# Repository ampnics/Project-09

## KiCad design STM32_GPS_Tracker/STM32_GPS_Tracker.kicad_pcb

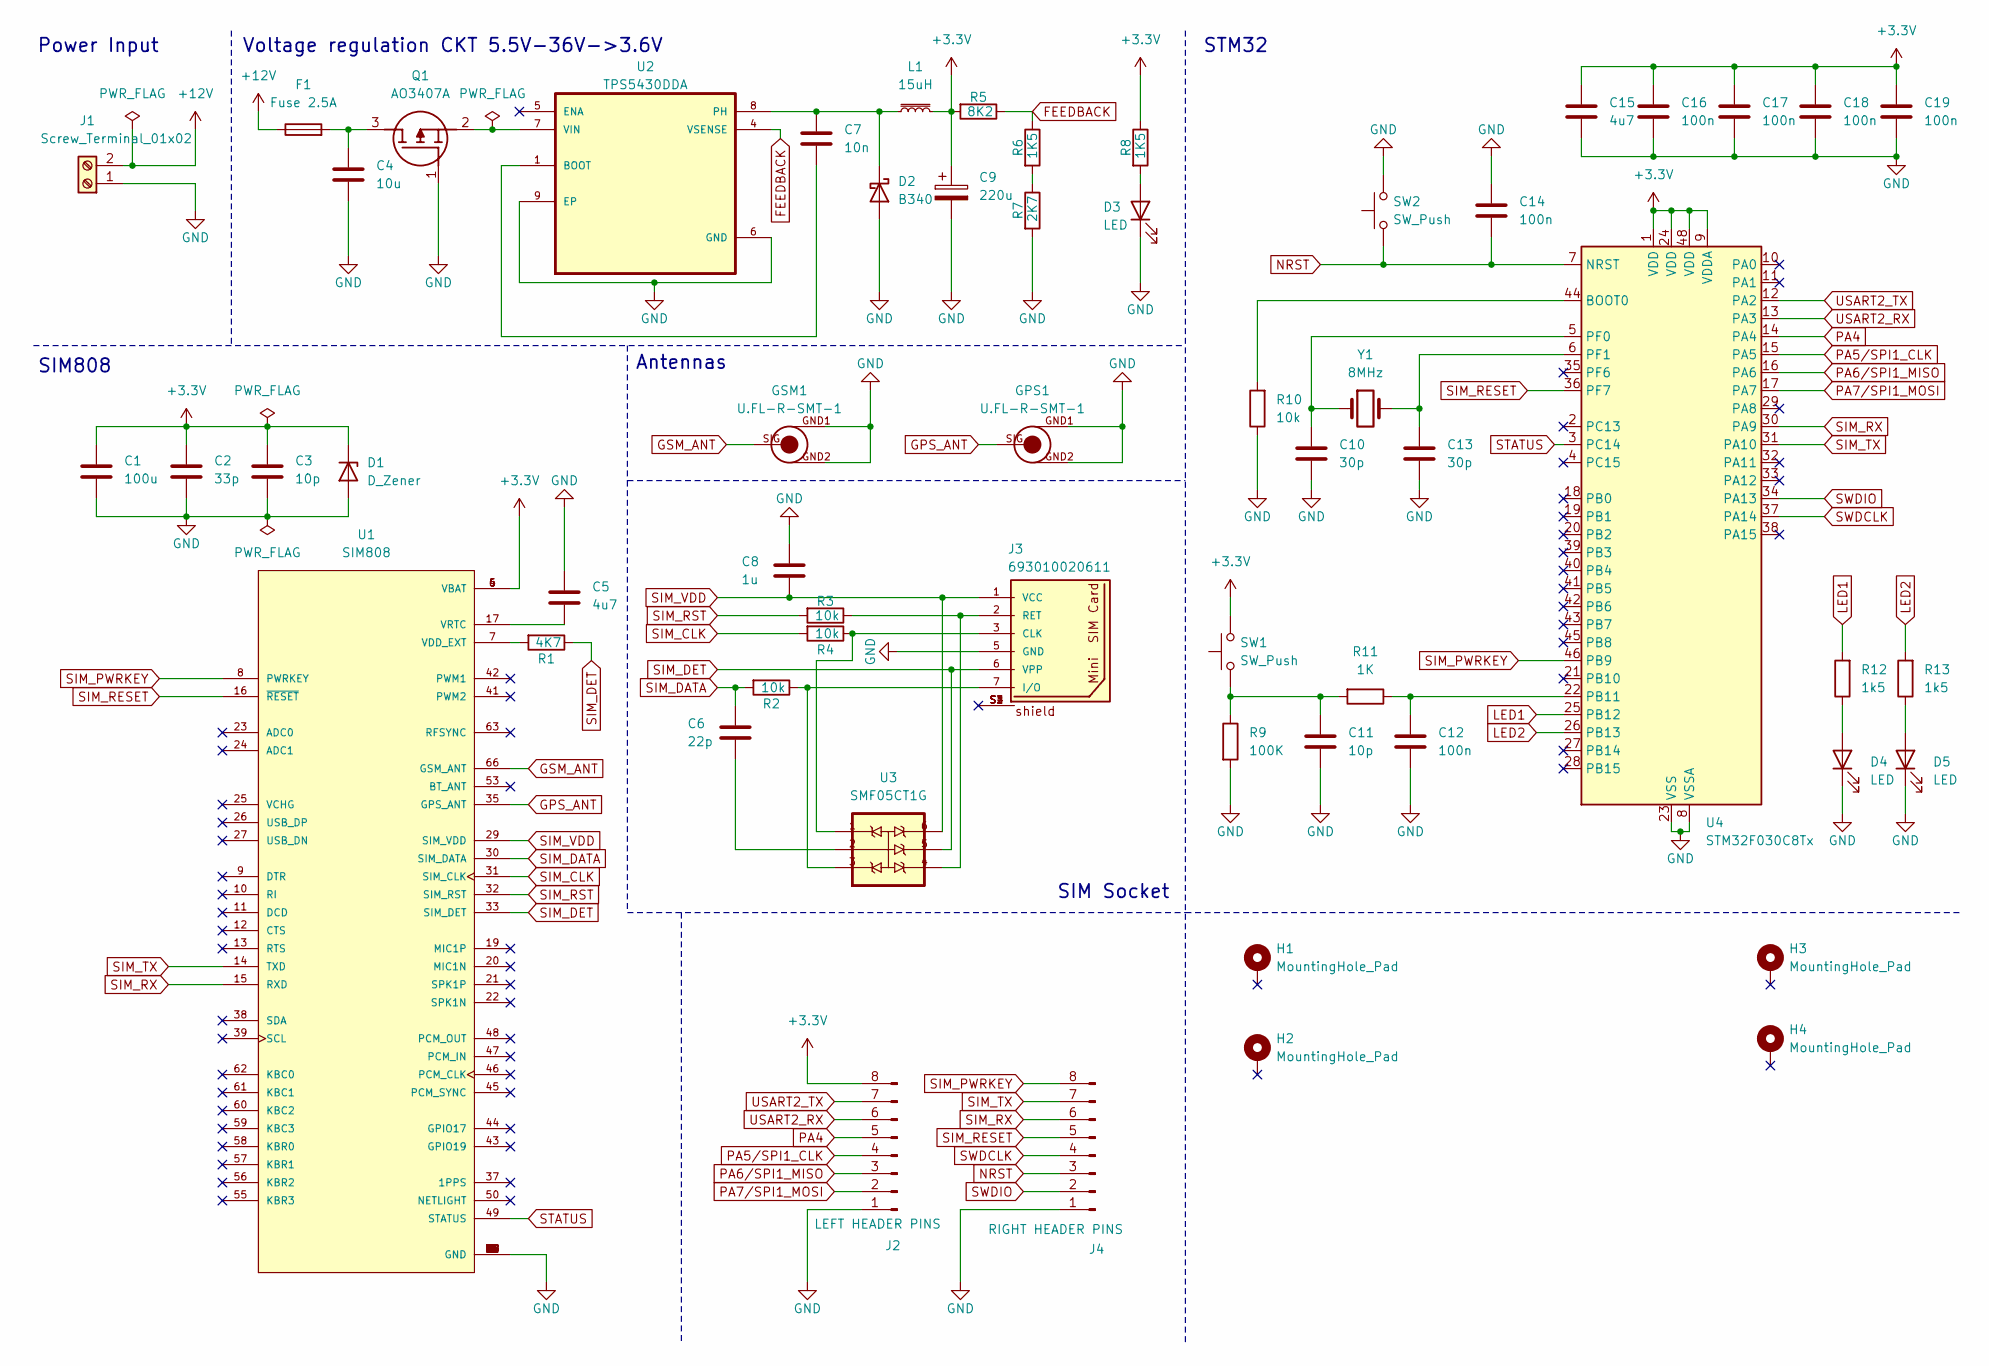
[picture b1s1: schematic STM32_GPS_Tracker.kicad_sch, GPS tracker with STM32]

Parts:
C1: 100u; C_1206_3216Metric
C2: 33p; C_0402_1005Metric
C3, C11: 10p; C_0402_1005Metric
C4: 10u; C_0805_2012Metric
C5, C15: 4u7; C_0201_0603Metric
C6: 22p; C_0402_1005Metric
C7: 10n; C_0201_0603Metric
C8: 1u; C_0402_1005Metric
C9: 220u; CP_EIA-7343-15_Kemet-W
C10, C13: 30p; C_0402_1005Metric
C12, C14, C16, C17, C18, C19: 100n; C_0402_1005Metric
D1: D_Zener; D_0805_2012Metric
D2: B340; D_SMC
D3, D4, D5: LED; LED_0603_1608Metric
F1: Fuse 2.5A; Fuse_0402_1005Metric
GPS1: U.FL-R-SMT-1
GSM1: U.FL-R-SMT-1
H1, H2, H3, H4: MountingHole_Pad; MountingHole_2.2mm_M2_Pad_Via
J1: Screw_Terminal_01x02; TerminalBlock_bornier-2_P5.08mm
J2: LEFT HEADER PINS; PinHeader_1x08_P2.54mm_Vertical
J3: 693010020611; PART-NUMBER 693010020611
J4: RIGHT HEADER PINS; PinHeader_1x08_P2.54mm_Vertical
L1: 15uH; L_10.4x10.4_H4.8
Q1: AO3407A; SOT95P280X125-3N; Manufacturer_Part_Number AO3407A
R1: 4K7; R_0402_1005Metric
R2, R3, R4, R10: 10k; R_0402_1005Metric
R5: 8K2; R_0805_2012Metric
R6, R8: 1K5; R_0805_2012Metric
R7: 2K7; R_0805_2012Metric
R9: 100K; R_0201_0603Metric
R11: 1K; R_0603_1608Metric
R12, R13: 1k5; R_0805_2012Metric
SW1, SW2: SW_Push; SW_Push_1P1T_NO_CK_KSC6xxJ
U1: SIM808; XCVR_SIM808; PARTREV 1.03
U2: TPS5430DDA; VREG_LM5017MR_NOPB
U3: SMF05CT1G; SOT65P210X110-6N
U4: STM32F030C8Tx; LQFP-48_7x7mm_P0.5mm
Y1: 8MHz; Crystal_SMD_5032-2Pin_5.0x3.2mm

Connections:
+3.3V: C1.1, C2.1, C3.1, C9.1, C15.1, C16.1, C17.1, C18.1, C19.1, D1.1 (K), J2.8, L1.2, R5.2, R8.1, SW1.2, U1.4 (VBAT), U1.5 (VBAT), U1.6 (VBAT), U4.1 (VDD), U4.9 (VDDA), U4.24 (VDD), U4.48 (VDD); also elsewhere on the board
+12V: F1.1, J1.2
FEEDBACK: R5.1, R6.1, U2.4 (VSENSE)
GND: C1.2, C2.2, C3.2, C4.2, C5.1, C8.1, C9.2, C10.2, C11.2, C12.2, C13.2, C14.1, C15.2, C16.2, C17.2, C18.2, C19.2, D1.2 (A), D2.2 (A), D3.1 (K), D4.1 (K), D5.1 (K), GPS1.GND1, GPS1.GND2, GSM1.GND1, GSM1.GND2, J1.1, J2.1, J3.5 (GND), J4.1, Q1.1 (G), R7.2, R9.2, R10.1, SW2.2, U1.1 (GND), U1.2 (GND), U1.3 (GND), U1.18 (GND), U1.28 (GND), U1.34 (GND), U1.36 (GND), U1.40 (GND), U1.51 (GND), U1.52 (GND), U1.54 (GND), U1.64 (GND), U1.65 (GND), U1.67 (GND), U1.68 (GND), U2.6 (GND), U2.9 (EP), U4.8 (VSSA), U4.23 (VSS), U4.47 (VSS); also elsewhere on the board
GPS_ANT: GPS1.SIG, U1.35 (GPS_ANT)
GSM_ANT: GSM1.SIG, U1.66 (GSM_ANT)
LED1: R12.2, U4.25 (PB12)
LED2: R13.2, U4.26 (PB13)
NRST: C14.2, J4.3, SW2.1, U4.7 (NRST); also elsewhere on the board
unnamed: C6.2, U3.2
unnamed 10: C11.1, R9.1, R11.2, SW1.1; also elsewhere on the board
unnamed: C7.2, D2.1 (K), L1.1, U2.8 (PH)
unnamed: D3.2 (A), R8.2
unnamed: D4.2 (A), R12.1
unnamed: D5.2 (A), R13.1
unnamed: J3.3 (CLK), R4.1, U3.1
unnamed: J3.7 (I/O), R2.1, U3.3
unnamed: J3.2 (RET), R3.1, U3.4
unnamed: C4.1, F1.2, Q1.3 (D)
unnamed: Q1.2 (S), U2.7 (VIN)
unnamed: R6.2, R7.1
unnamed: R1.2, U1.7 (VDD_EXT)
unnamed: C5.2, U1.17 (VRTC)
unnamed: C7.1, U2.1 (BOOT)
unnamed: R10.2, U4.44 (BOOT0)
unnamed: C12.1, R11.1, U4.22 (PB11)
unnamed: C10.1, U4.5 (PF0), Y1.1
unnamed: C13.1, U4.6 (PF1), Y1.2
PA4: J2.5, U4.14 (PA4)
PA5/SPI1_CLK: J2.4, U4.15 (PA5)
PA6/SPI1_MISO: J2.3, U4.16 (PA6)
PA7/SPI1_MOSI: J2.2, U4.17 (PA7)
SIM_CLK: R4.2, U1.31 (SIM_CLK)
SIM_DATA: C6.1, R2.2, U1.30 (SIM_DATA)
SIM_DET: J3.6 (VPP), R1.1, U1.33 (SIM_DET), U3.5
SIM_PWRKEY: J4.8, U1.8 (PWRKEY), U4.46 (PB9)
SIM_RESET: J4.5, U1.16 (~RESET), U4.36 (PF7)
SIM_RST: R3.2, U1.32 (SIM_RST)
SIM_RX: J4.6, U1.15 (RXD), U4.30 (PA9)
SIM_TX: J4.7, U1.14 (TXD), U4.31 (PA10)
SIM_VDD: C8.2, J3.1 (VCC), U1.29 (SIM_VDD), U3.6
STATUS: U1.49 (STATUS), U4.3 (PC14)
SWDCLK: J4.4, U4.37 (PA14)
SWDIO: J4.2, U4.34 (PA13)
USART2_RX: J2.6, U4.13 (PA3)
USART2_TX: J2.7, U4.12 (PA2)

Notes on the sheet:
SIM Socket
Power Input
Voltage regulation CKT 5.5V-36V->3.6V
STM32
Antennas
SIM808

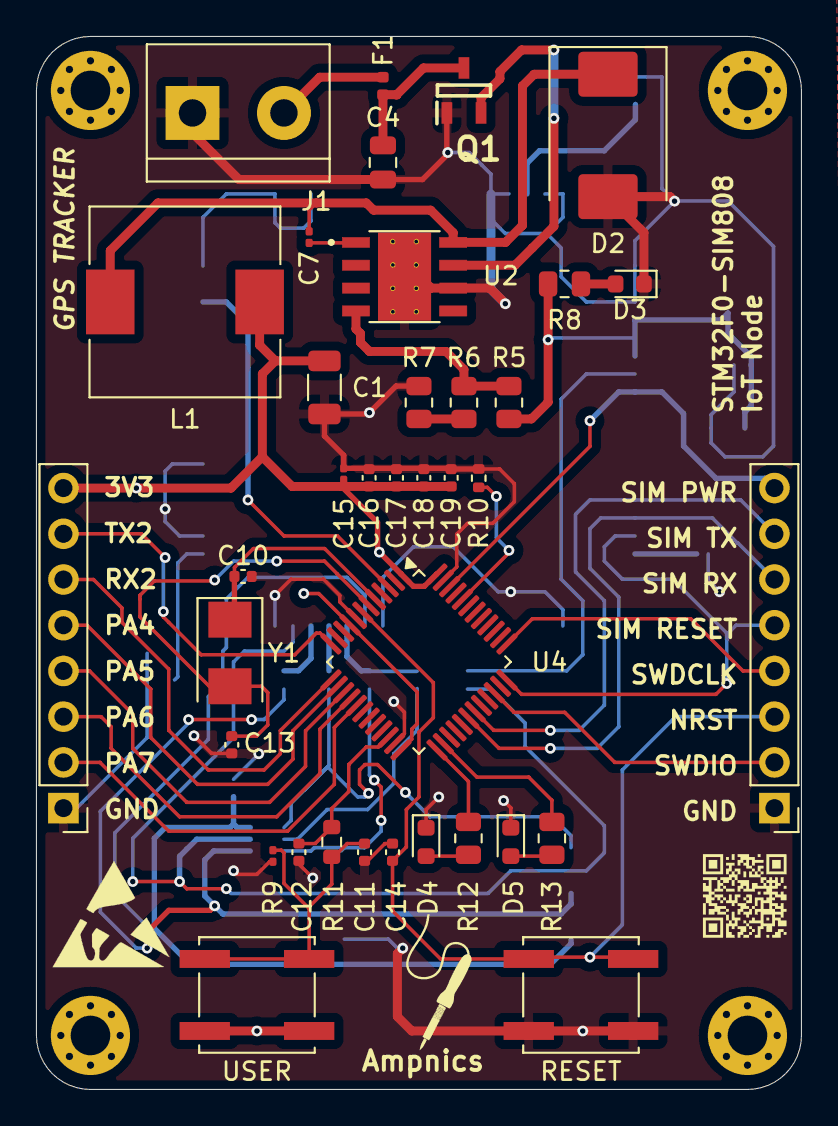
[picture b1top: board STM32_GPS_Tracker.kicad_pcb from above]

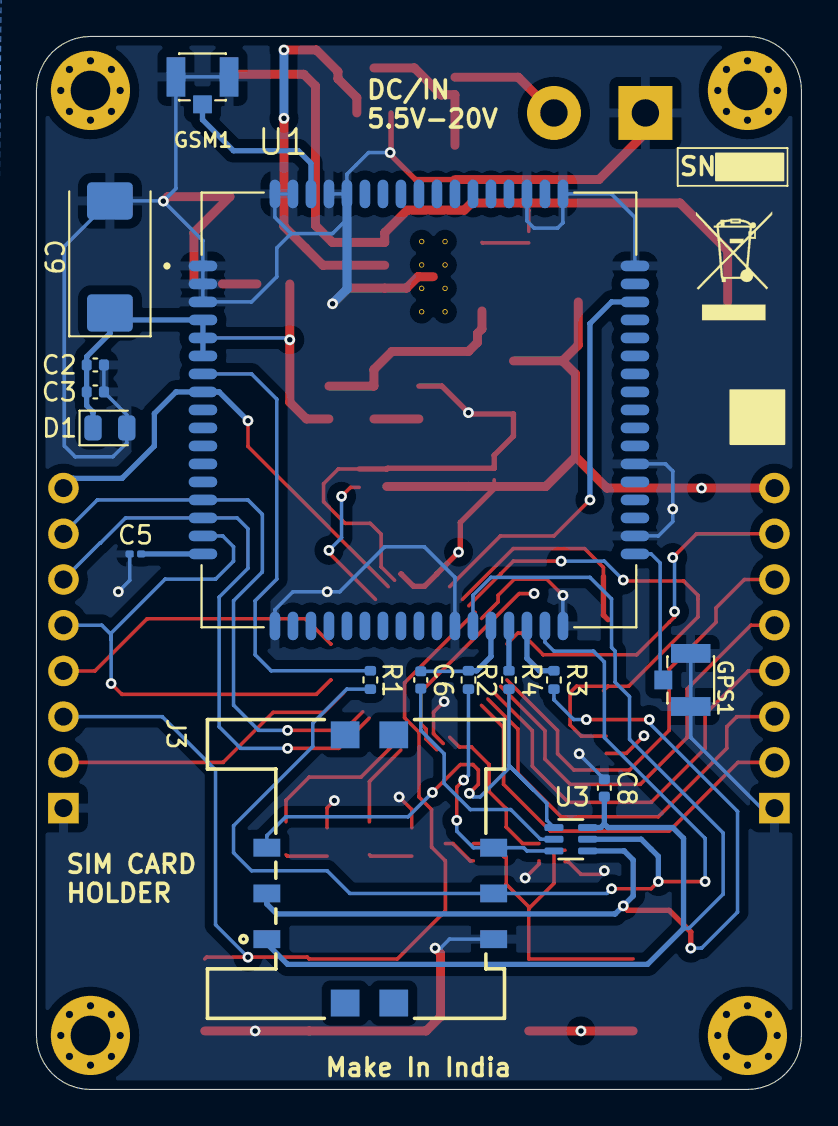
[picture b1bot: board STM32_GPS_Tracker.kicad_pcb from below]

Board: 4 copper layers, 42.5 x 58.5 mm, 57 parts (16 on the bottom side), 46 nets.

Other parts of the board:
RESET: SW_Push; SW_Push_1P1T_NO_CK_KSC6xxJ
USER: SW_Push; SW_Push_1P1T_NO_CK_KSC6xxJ

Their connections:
+3.3V: USER.2; also elsewhere on the board
GND: RESET.2; also elsewhere on the board
NRST: RESET.1; also elsewhere on the board
unnamed 10: USER.1; also elsewhere on the board

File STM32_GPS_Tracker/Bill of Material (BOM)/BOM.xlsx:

Reference | Value | Footprint | Qty
C1 | 100u | Capacitor_SMD:C_1206_3216Metric | 1
C2 | 33p | Capacitor_SMD:C_0402_1005Metric | 1
C3,C11 | 10p | Capacitor_SMD:C_0402_1005Metric | 2
C4 | 10u | Capacitor_SMD:C_0805_2012Metric | 1
C5,C15 | 4u7 | Capacitor_SMD:C_0201_0603Metric | 2
C6 | 22p | Capacitor_SMD:C_0402_1005Metric | 1
C7 | 10n | Capacitor_SMD:C_0201_0603Metric | 1
C8 | 1u | Capacitor_SMD:C_0402_1005Metric | 1
C9 | 220u | Capacitor_Tantalum_SMD:CP_EIA-7343-15_Kemet-W | 1
C10,C13 | 30p | Capacitor_SMD:C_0402_1005Metric | 2
C12,C14,C16,C17,C18,C19 | 100n | Capacitor_SMD:C_0402_1005Metric | 6
D1 | D_Zener | Diode_SMD:D_0805_2012Metric | 1
D2 | B340 | Diode_SMD:D_SMC | 1
D3,D4,D5 | LED | LED_SMD:LED_0603_1608Metric | 3
F1 | Fuse 2.5A | Fuse:Fuse_0402_1005Metric | 1
GPS1,GSM1 | U.FL-R-SMT-1 | U.FL-R-SMT-1:U.FL-R-SMT-1 | 2
J1 | Screw_Terminal_01x02 | TerminalBlock:TerminalBlock_bornier-2_P5.08mm | 1
J2 | LEFT HEADER PINS | Connector_PinHeader_2.54mm:PinHeader_1x08_P2.54mm_Vertical | 1
J3 | 693000000000 | 693010020611:693010020611 | 1
J4 | RIGHT HEADER PINS | Connector_PinHeader_2.54mm:PinHeader_1x08_P2.54mm_Vertical | 1
L1 | 15uH | Inductor_SMD:L_10.4x10.4_H4.8 | 1
Q1 | AO3407A | LIB_AO3407A:SOT95P280X125-3N | 1
R1 | 4K7 | Resistor_SMD:R_0402_1005Metric | 1
R2,R3,R4,R10 | 10k | Resistor_SMD:R_0402_1005Metric | 4
R5 | 8K2 | Resistor_SMD:R_0805_2012Metric | 1
R6,R8 | 1K5 | Resistor_SMD:R_0805_2012Metric | 2
R7 | 2K7 | Resistor_SMD:R_0805_2012Metric | 1
R9 | 100K | Resistor_SMD:R_0201_0603Metric | 1
R11 | 1K | Resistor_SMD:R_0603_1608Metric | 1
R12,R13 | 1k5 | Resistor_SMD:R_0805_2012Metric | 2
SW1,SW2 | SW_Push | Button_Switch_SMD:SW_Push_1P1T_NO_CK_KSC6xxJ | 2
U1 | SIM808 | SIM808:XCVR_SIM808 | 1
U2 | TPS5430DDA | TPS5430DDA:VREG_LM5017MR_NOPB | 1
U3 | SMF05CT1G | SMF05CT1G:SOT65P210X110-6N | 1
U4 | STM32F030C8Tx | Package_QFP:LQFP-48_7x7mm_P0.5mm | 1
Y1 | 8MHz | Crystal:Crystal_SMD_5032-2Pin_5.0x3.2mm | 1
